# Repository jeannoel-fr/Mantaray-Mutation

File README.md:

# Mantaray-Mutation
First version of Mantaray Keyboard.

I love the design and ergonomy of the <a href="https://github.com/davidphilipbarr/Sweep/"> Ferris Sweep </a>. However, I often use graphical software - it means I often have a mouse in the right hand, and use the keyboard to trigger shortcuts. 

Mantaray Mutation is a attempt to keep the ergonomic shape of the Ferris Sweep, but:
- monobloc
- with one num row
- with 2 keys dedicated to shift and ctrl ( as mouse modifier )
- with a small lcd - to show wich layer is active

It's based on the great work of <a href="https://github.com/tuxedocurly/mantaray_keyboard">Colton Hawkins</a>, who created the Mantaray Keyboard.

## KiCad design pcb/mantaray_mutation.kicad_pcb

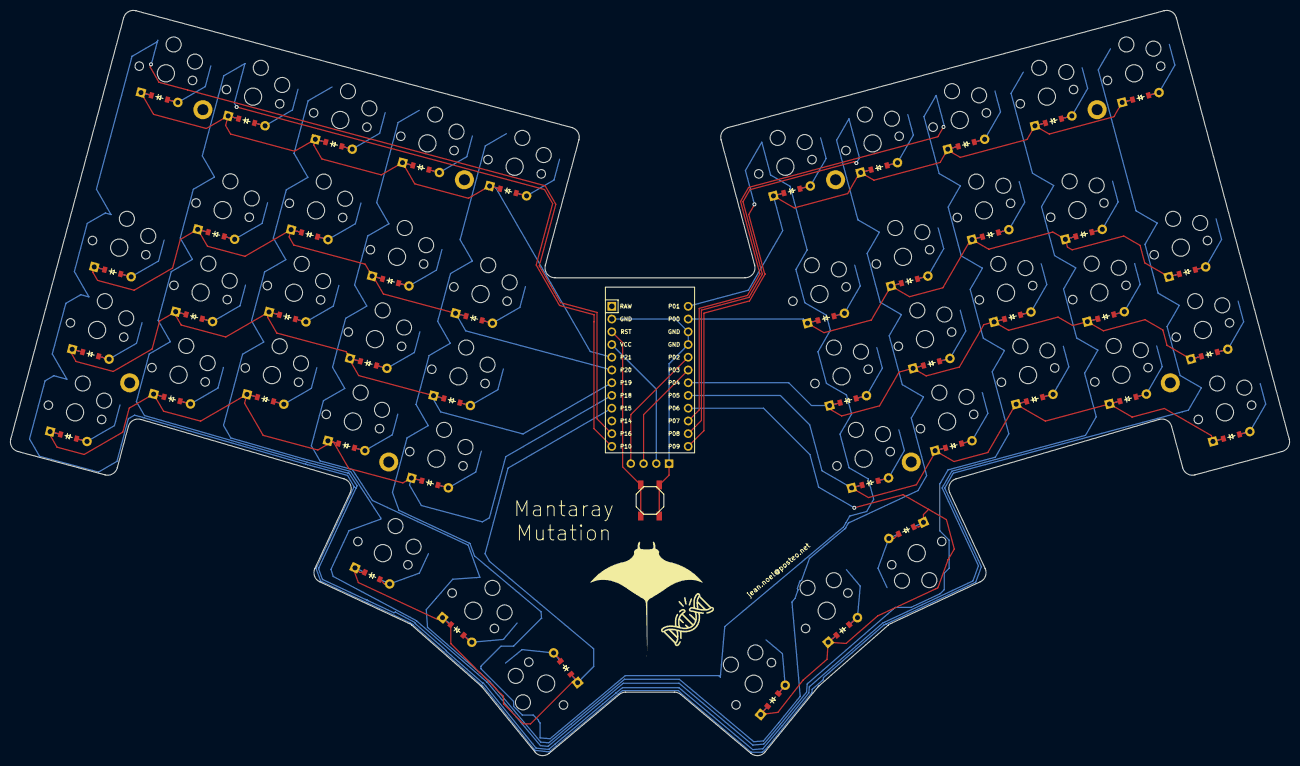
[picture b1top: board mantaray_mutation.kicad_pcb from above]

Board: 2 copper layers, 255.1 x 148.6 mm, 103 parts (0 on the bottom side), 66 nets.

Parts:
B1: SW_TACT_ALPS_SKQGABE010
D1, D2, D3, D4, D5, D6, D7, D8, D9, D10, D11, D12, D13, D14, D15, D16, D17, D18, D19, D20, D21, D22, D23, D24, D25, D26, D27, D28, D29, D30, D31, D32, D33, D34, D35, D36, D37, D38, D39, D40, D41, D42, D43, D44, D45, D46: ComboDiode
H1, H2, H3, H4, H5, H6, H7, H8: mounting_hole_plated
MCU1: ProMicro
OLED1: OLED; OLED_headers
S1, S2, S3, S4, S5, S6, S7, S8, S9, S10, S11, S12, S13, S14, S15, S16, S17, S18, S19, S20, S21, S22, S23, S24, S25, S26, S27, S28, S29, S30, S31, S32, S33, S34, S35, S36, S37, S38, S39, S40, S41, S42, S43, S44, S45, S46: PG1350

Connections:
GND: B1.1, MCU1.2, MCU1.15, MCU1.16, OLED1.1
P0: D26.1, D29.1, D32.1, D35.1, D38.1, MCU1.14
P1: D39.1, D40.1, D41.1, D42.1, D43.1, MCU1.13
P2: MCU1.17, OLED1.4
P3: MCU1.18, OLED1.3
P4: D25.1, D28.1, D31.1, D34.1, D37.1, MCU1.19
P5: D24.1, D27.1, D30.1, D33.1, D36.1, MCU1.20
P6: D44.1, D45.1, D46.1, MCU1.21
P7: MCU1.22, S7.1, S8.1, S9.1, S18.1, S21.1, S30.1, S31.1, S32.1, S41.1, S44.1
P8: MCU1.23, S10.1, S11.1, S12.1, S19.1, S22.1, S33.1, S34.1, S35.1, S42.1, S45.1
P9: MCU1.24, S13.1, S14.1, S15.1, S20.1, S23.1, S36.1, S37.1, S38.1, S43.1, S46.1
P10: MCU1.12, S4.1, S5.1, S6.1, S17.1, S27.1, S28.1, S29.1, S40.1
P15: D21.1, D22.1, D23.1, MCU1.9
P16: MCU1.11, S1.1, S2.1, S3.1, S16.1, S24.1, S25.1, S26.1, S39.1
P18: D1.1, D4.1, D7.1, D10.1, D13.1, MCU1.8
P19: D2.1, D5.1, D8.1, D11.1, D14.1, MCU1.7
P20: D3.1, D6.1, D9.1, D12.1, D15.1, MCU1.6
P21: D16.1, D17.1, D18.1, D19.1, D20.1, MCU1.5
RST: B1.2, MCU1.3
VCC: MCU1.4, OLED1.2
index_bottom: D10.2, S10.2
index_home: D11.2, S11.2
index_num: D19.2, S19.2
index_top: D12.2, S12.2
inner_bottom: D13.2, S13.2
inner_cluster: D23.2, S23.2
inner_home: D14.2, S14.2
inner_num: D20.2, S20.2
inner_top: D15.2, S15.2
layer_cluster: D21.2, S21.2
middle_bottom: D7.2, S7.2
middle_home: D8.2, S8.2
middle_num: D18.2, S18.2
middle_top: D9.2, S9.2
mirror_index_bottom: D33.2, S33.2
mirror_index_home: D34.2, S34.2
mirror_index_num: D42.2, S42.2
mirror_index_top: D35.2, S35.2
mirror_inner_bottom: D36.2, S36.2
mirror_inner_cluster: D46.2, S46.2
mirror_inner_home: D37.2, S37.2
mirror_inner_num: D43.2, S43.2
mirror_inner_top: D38.2, S38.2
mirror_layer_cluster: D44.2, S44.2
mirror_middle_bottom: D30.2, S30.2
mirror_middle_home: D31.2, S31.2
mirror_middle_num: D41.2, S41.2
mirror_middle_top: D32.2, S32.2
mirror_pinky_bottom: D24.2, S24.2
mirror_pinky_home: D25.2, S25.2
mirror_pinky_num: D39.2, S39.2
mirror_pinky_top: D26.2, S26.2
mirror_ring_bottom: D27.2, S27.2
mirror_ring_home: D28.2, S28.2
mirror_ring_num: D40.2, S40.2
mirror_ring_top: D29.2, S29.2
mirror_space_cluster: D45.2, S45.2
pinky_bottom: D1.2, S1.2
pinky_home: D2.2, S2.2
pinky_num: D16.2, S16.2
pinky_top: D3.2, S3.2
ring_bottom: D4.2, S4.2
ring_home: D5.2, S5.2
ring_num: D17.2, S17.2
ring_top: D6.2, S6.2
space_cluster: D22.2, S22.2

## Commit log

2025-04-25 ergogen conf
2025-04-25 initial push
2025-04-28 ajout qmk_config
